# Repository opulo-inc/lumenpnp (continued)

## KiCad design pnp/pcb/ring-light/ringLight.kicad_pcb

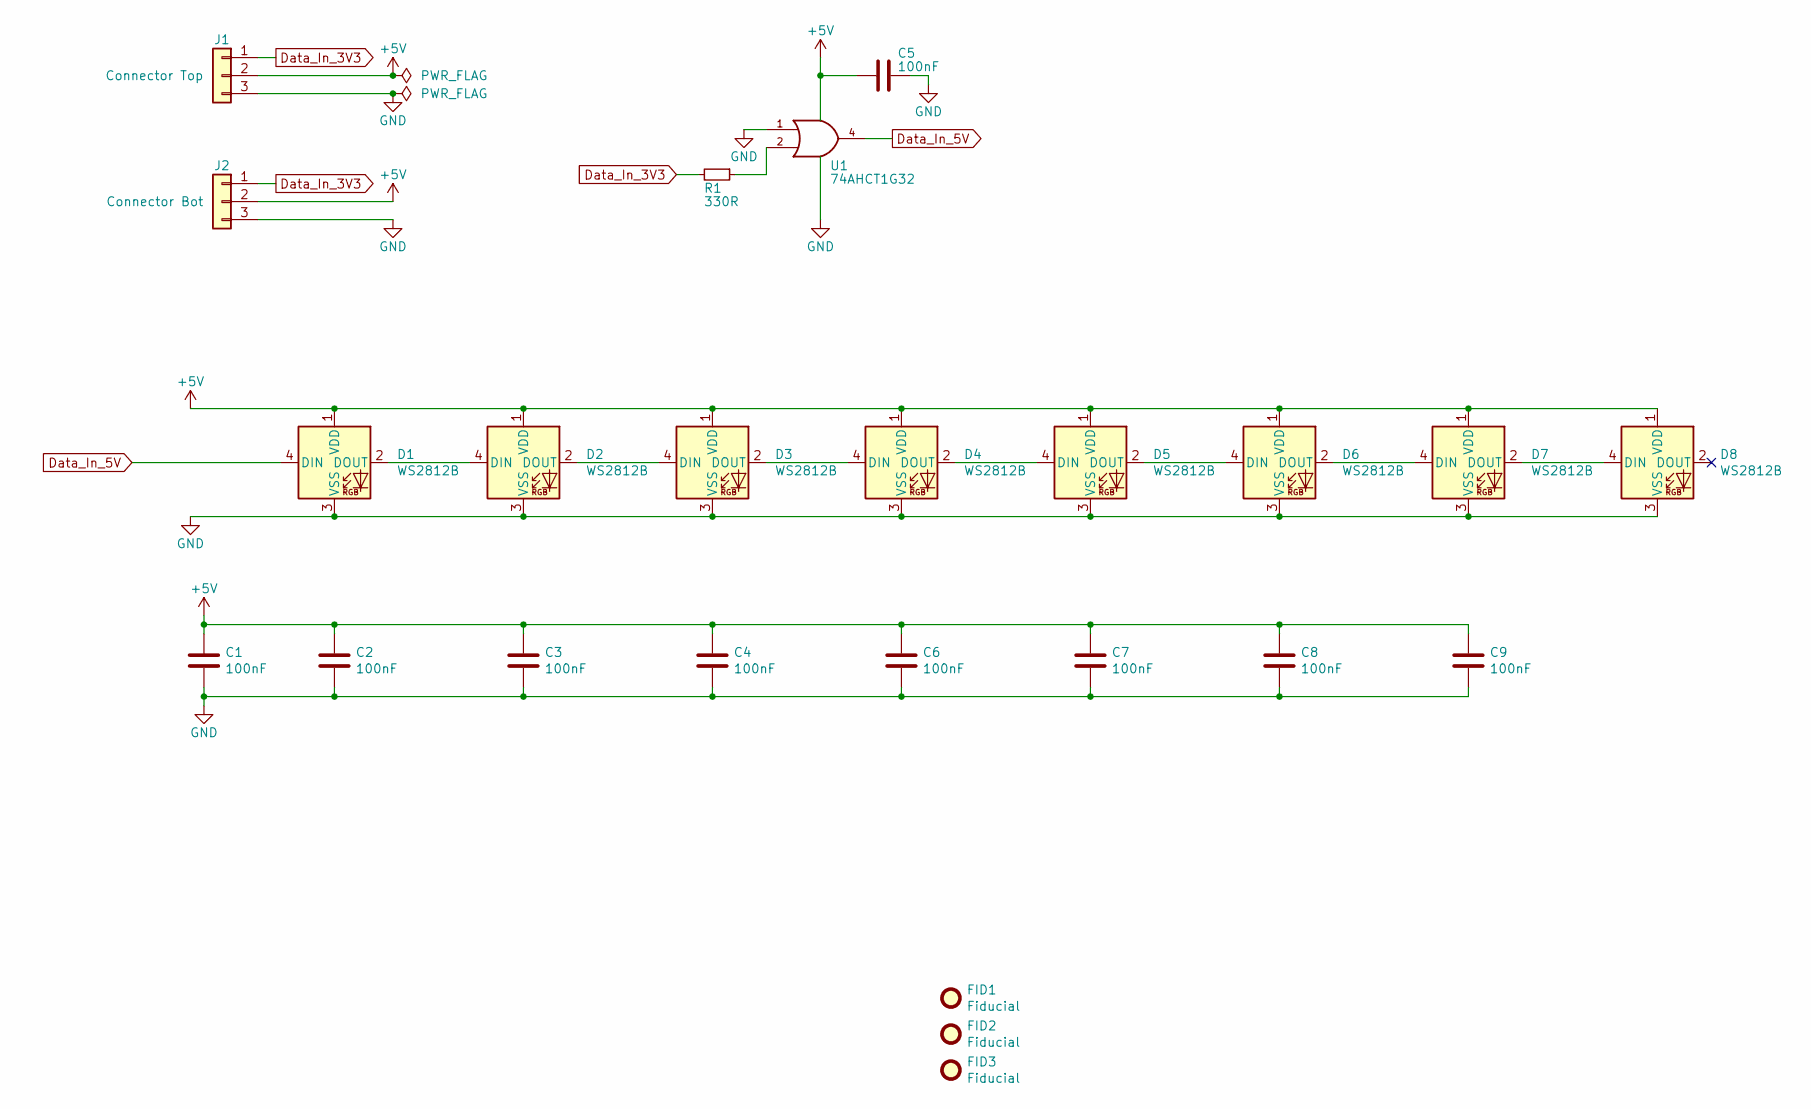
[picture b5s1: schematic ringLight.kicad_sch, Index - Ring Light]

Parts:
C1, C2, C3, C4, C5, C6, C7, C8, C9: 100nF; C_0805_2012Metric; Part # CC0805KRX7R9BB104; JLCPCB C49678
D1, D2, D3, D4, D5, D6, D7, D8: WS2812B; LED_WS2812B_PLCC4_5.0x5.0mm_P3.2mm; Part # WS2812B; JLCPCB C114586
FID1, FID2, FID3: Fiducial; Fiducial_1mm_Mask2mm
J1: Connector Top; JST_XH_B3B-XH-A_1x03_P2.50mm_Vertical; Part # B3B-XH-A(LF)(SN); JLCPCB C144394
J2: Connector Bot; JST_XH_S3B-XH-A-1_1x03_P2.50mm_Horizontal; Part # S3B-XH-A-1(LF)(SN); JLCPCB C163036
R1: 330R; R_0805_2012Metric; Part # 0805W8F3300T5E; JLCPCB C17630
U1: 74AHCT1G32; SOT-353_SC-70-5; Part # SN74AHCT1G32DCKR; JLCPCB C350558

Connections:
+5V: C1.1, C2.1, C3.1, C4.1, C5.1, C6.1, C7.1, C8.1, C9.1, D1.1 (VDD), D2.1 (VDD), D3.1 (VDD), D4.1 (VDD), D5.1 (VDD), D6.1 (VDD), D7.1 (VDD), D8.1 (VDD), J1.2, J2.2, U1.5 (VCC)
Data_In_3V3: J1.1, J2.1, R1.2
Data_In_5V: D1.4 (DIN), U1.4
GND: C1.2, C2.2, C3.2, C4.2, C5.2, C6.2, C7.2, C8.2, C9.2, D1.3 (VSS), D2.3 (VSS), D3.3 (VSS), D4.3 (VSS), D5.3 (VSS), D6.3 (VSS), D7.3 (VSS), D8.3 (VSS), J1.3, J2.3, U1.1, U1.3 (GND)
unnamed: D1.2 (DOUT), D2.4 (DIN)
unnamed: D2.2 (DOUT), D3.4 (DIN)
unnamed: D3.2 (DOUT), D4.4 (DIN)
unnamed: D4.2 (DOUT), D5.4 (DIN)
unnamed: D5.2 (DOUT), D6.4 (DIN)
unnamed: D6.2 (DOUT), D7.4 (DIN)
unnamed: D7.2 (DOUT), D8.4 (DIN)
unnamed: R1.1, U1.2

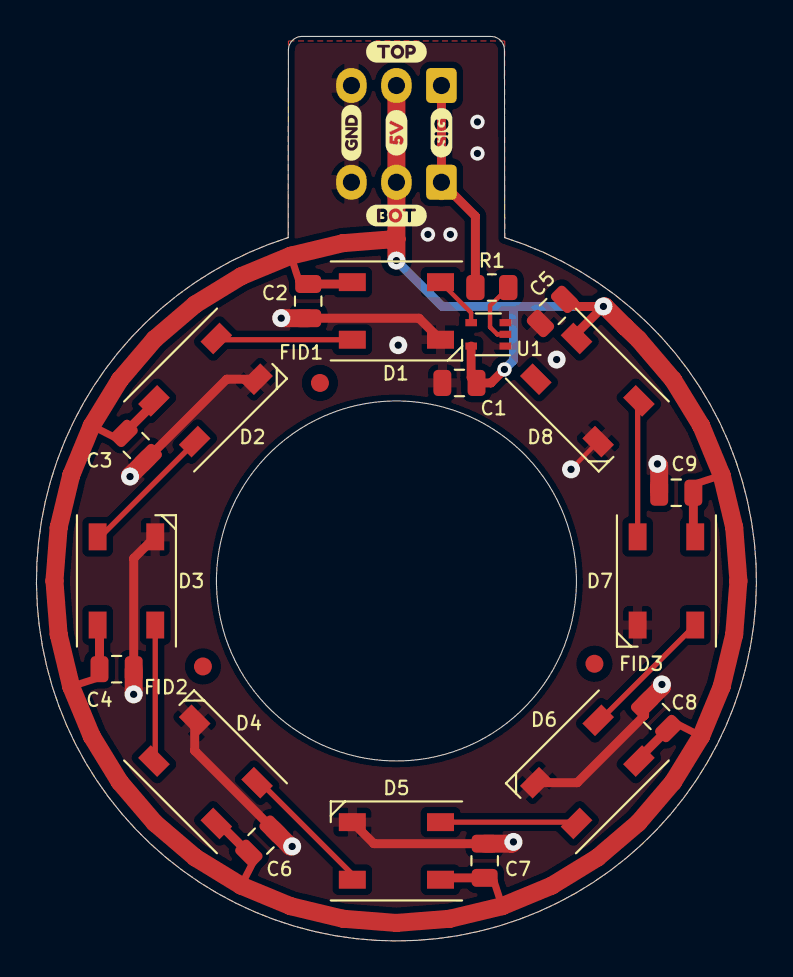
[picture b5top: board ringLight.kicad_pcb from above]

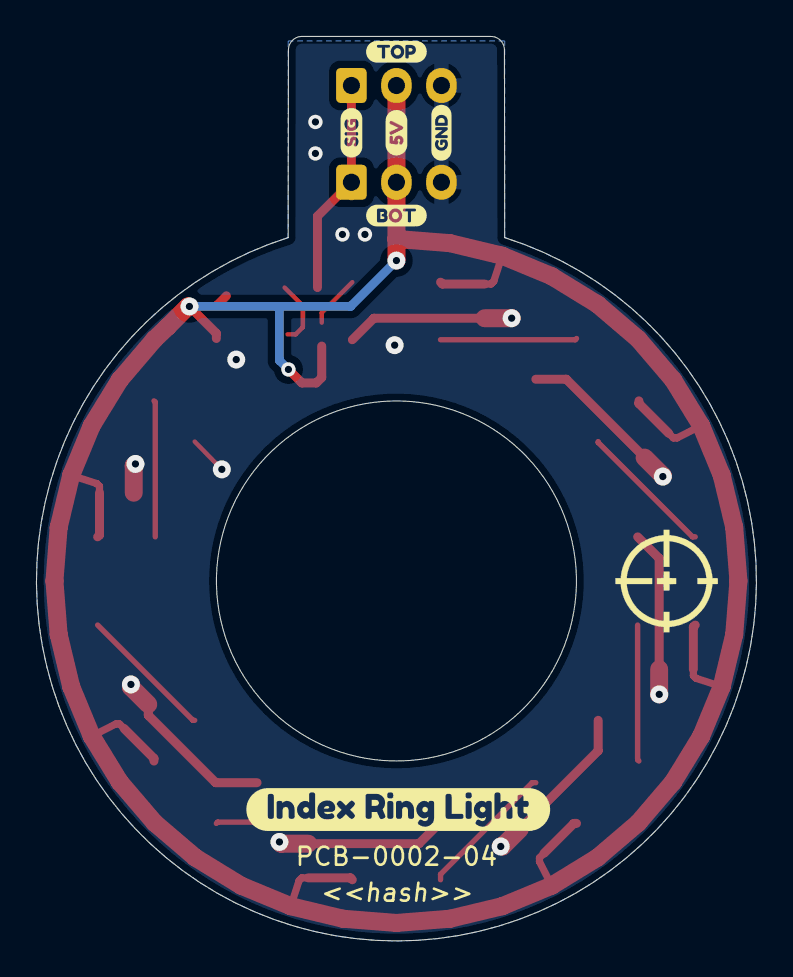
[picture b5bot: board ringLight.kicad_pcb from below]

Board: 2 copper layers, 40.0 x 50.2 mm, 36 parts (8 on the bottom side), 12 nets.

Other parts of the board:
LOGO: LOGO; logo
kibuzzard-61F2BC8D, kibuzzard-61F2BC8D#2: G***; kibuzzard-61F2BC8D
kibuzzard-61F2BC9E, kibuzzard-61F2BC9E#2: G***; kibuzzard-61F2BC9E
kibuzzard-61F2BC96, kibuzzard-61F2BC96#2: G***; kibuzzard-61F2BC96
kibuzzard-61F2BEFE: G***; kibuzzard-61F2BEFE
kibuzzard-61F2BF3C: G***; kibuzzard-61F2BF3C
kibuzzard-61F2BF4A: G***; kibuzzard-61F2BF4A
kibuzzard-61F2BF10: G***; kibuzzard-61F2BF10
svg2mod: n/a; label

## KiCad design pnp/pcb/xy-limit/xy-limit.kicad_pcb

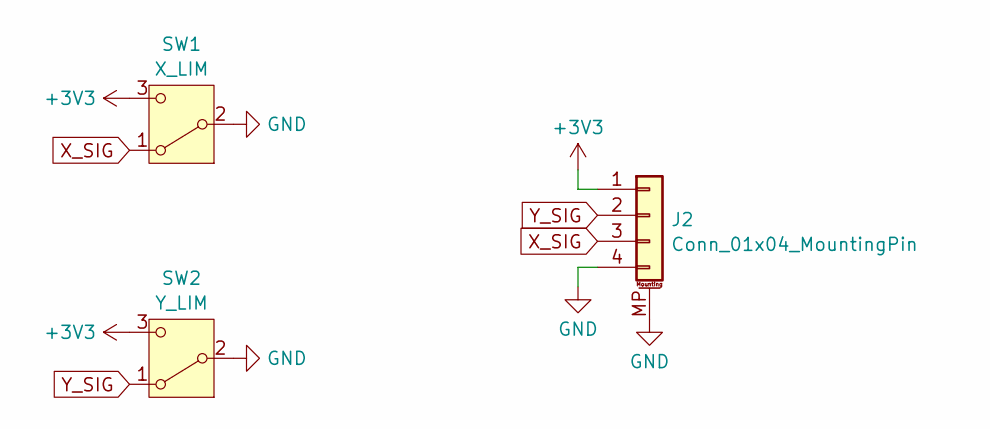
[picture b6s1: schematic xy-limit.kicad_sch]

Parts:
J2: Conn_01x04_MountingPin; JST_PH_B4B-PH-SM4-TB_1x04-1MP_P2.00mm_Vertical
SW1: X_LIM; D2FS-FL-N-A
SW2: Y_LIM; D2FS-FL-N

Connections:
+3V3: J2.1, SW1.3 (C), SW2.3 (C)
GND: J2.4, J2.MP (MountPin), SW1.2 (B), SW2.2 (B)
X_SIG: J2.3, SW1.1 (A)
Y_SIG: J2.2, SW2.1 (A)

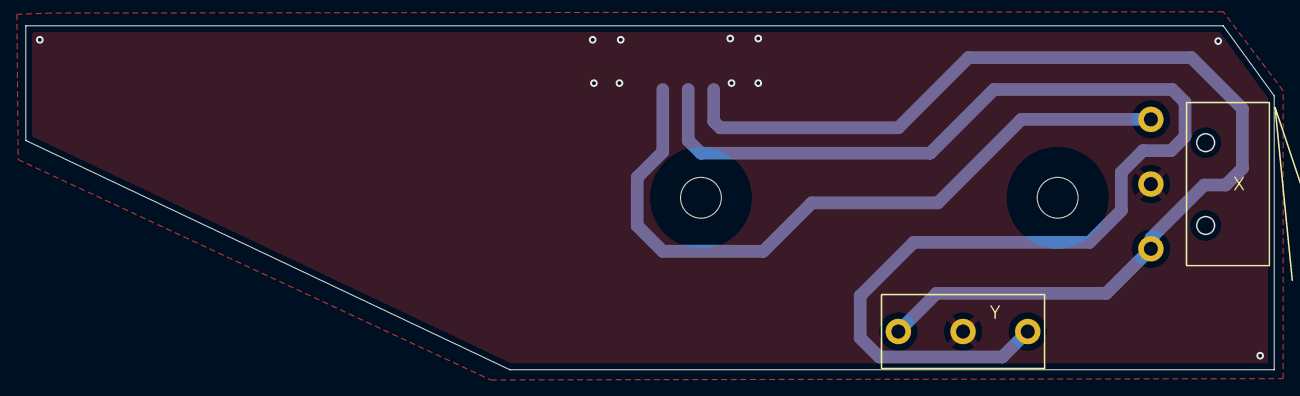
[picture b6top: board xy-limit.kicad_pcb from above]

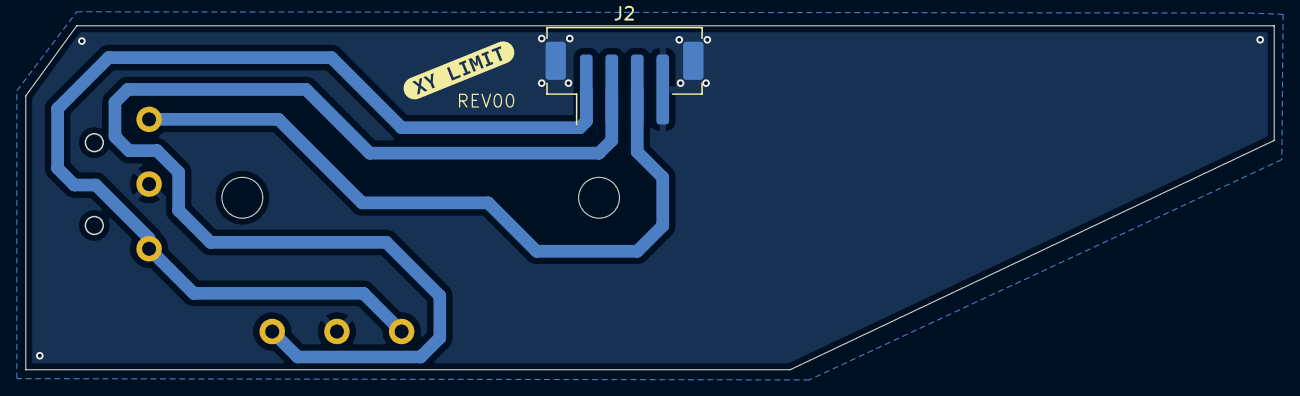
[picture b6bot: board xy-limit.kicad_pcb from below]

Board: 2 copper layers, 98.0 x 27.0 mm, 4 parts (2 on the bottom side), 4 nets.

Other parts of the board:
kibuzzard-65F47CEB: G***; kibuzzard-65F47CEB

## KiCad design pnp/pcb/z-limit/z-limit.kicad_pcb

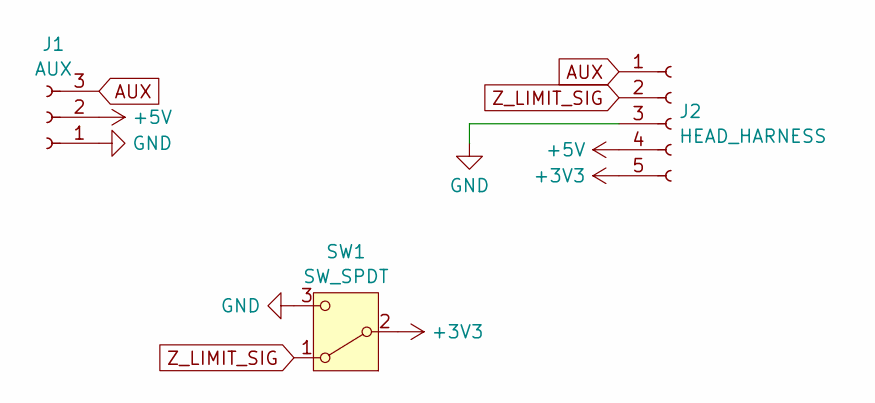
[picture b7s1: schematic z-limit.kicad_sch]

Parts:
J1: AUX; JST_PH_S3B-PH-K_1x03_P2.00mm_Horizontal
J2: HEAD_HARNESS; JST_PH_B5B-PH-SM4-TB_1x05-1MP_P2.00mm_Vertical
SW1: SW_SPDT; D2FS-FL-N-A

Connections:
+3V3: J2.5, SW1.2 (B)
+5V: J1.2, J2.4
AUX: J1.3, J2.1
GND: J1.1, J2.3, J2.MP, SW1.3 (C)
Z_LIMIT_SIG: J2.2, SW1.1 (A)

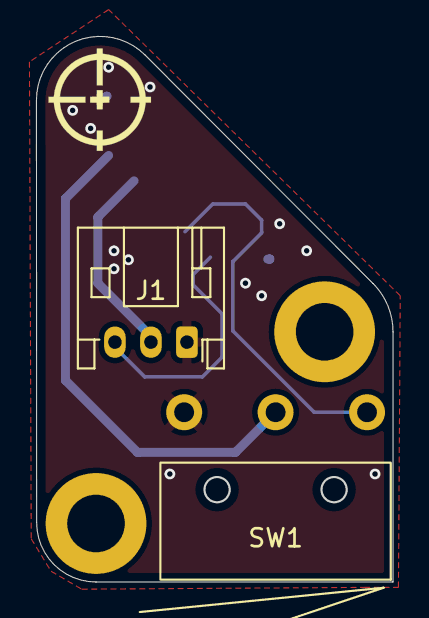
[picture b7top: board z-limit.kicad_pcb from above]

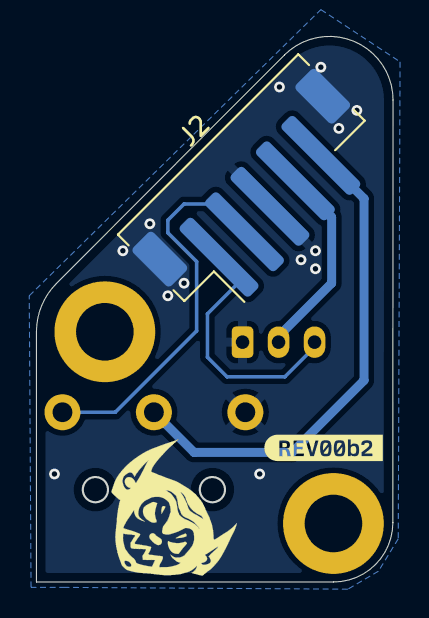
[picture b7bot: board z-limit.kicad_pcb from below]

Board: 2 copper layers, 19.8 x 30.3 mm, 4 parts (2 on the bottom side), 5 nets.

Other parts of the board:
kibuzzard-66478BBC: G***; kibuzzard-66478BBC

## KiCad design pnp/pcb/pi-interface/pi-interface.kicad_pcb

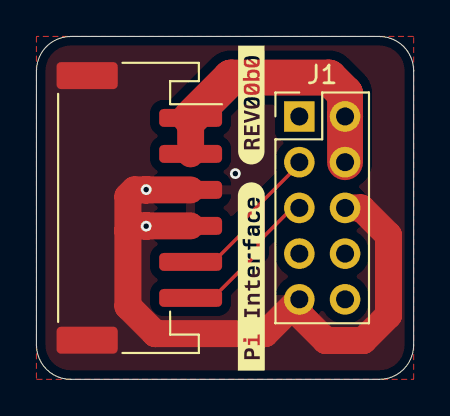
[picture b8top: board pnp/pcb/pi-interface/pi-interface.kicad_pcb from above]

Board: 2 copper layers, 21.0 x 19.1 mm, 4 parts (0 on the bottom side), 4 nets.

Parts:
J1: PI; PinHeader_2x05_P2.54mm_Vertical
Je: MOBO; JST_PH_S6B-PH-SM4-TB_1x06-1MP_P2.00mm_Horizontal
kibuzzard-6647A66F: G***; kibuzzard-6647A66F
kibuzzard-6647A648: G***; kibuzzard-6647A648

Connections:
+5V: J1.2, J1.4, Je.1, Je.2
BOOT: J1.3, Je.5
GND: J1.6, J1.9, Je.3, Je.4, Je.MP (MountPin)
RESET: J1.5, Je.6

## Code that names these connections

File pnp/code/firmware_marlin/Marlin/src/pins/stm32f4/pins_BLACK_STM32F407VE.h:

/**
 * Marlin 3D Printer Firmware
 * Copyright (c) 2020 MarlinFirmware [https://github.com/MarlinFirmware/Marlin]
 *
 * Based on Sprinter and grbl.
 * Copyright (c) 2011 Camiel Gubbels / Erik van der Zalm
 *
 * This program is free software: you can redistribute it and/or modify
 * it under the terms of the GNU General Public License as published by
 * the Free Software Foundation, either version 3 of the License, or
 * (at your option) any later version.
 *
 * This program is distributed in the hope that it will be useful,
 * but WITHOUT ANY WARRANTY; without even the implied warranty of
 * MERCHANTABILITY or FITNESS FOR A PARTICULAR PURPOSE.  See the
 * GNU General Public License for more details.
 *
 * You should have received a copy of the GNU General Public License
 * along with this program.  If not, see <https://www.gnu.org/licenses/>.
 *
 */
#pragma once

/**
 * STM32F407VET6 with RAMPS-like shield
 * 'Black' STM32F407VET6 board - https://www.stm32duino.com/viewtopic.php?t=485
 * Shield - https://github.com/jmz52/Hardware
 */

#if !defined(STM32F4) && !defined(STM32F4xx)
  #error "Oops! Select an STM32F4 board in 'Tools > Board.'"
#elif HOTENDS > 2 || E_STEPPERS > 2
  #error "Black STM32F4VET6 supports up to 2 hotends / E-steppers."
#endif

#ifndef BOARD_INFO_NAME
  #define BOARD_INFO_NAME "Black STM32F4VET6"
#endif

#define DEFAULT_MACHINE_NAME "Index PnP"

//#define I2C_EEPROM
#define SRAM_EEPROM_EMULATION
#define MARLIN_EEPROM_SIZE                0x2000  // 8KB

//
// Servos
//
#define SERVO0_PIN                          PC6
#define SERVO1_PIN                          PC7

//
// Limit Switches
//
#define X_MIN_PIN                           PC13
#define X_MAX_PIN                           PA15
#define Y_MIN_PIN                           PA5
#define Y_MAX_PIN                           PD12
#define Z_MIN_PIN                           PD14
#define Z_MAX_PIN                           PD15

//
// Steppers
//
#define X_STEP_PIN                          PD7
#define X_DIR_PIN                           PD6
#define X_ENABLE_PIN                        PB3

#define Y_STEP_PIN                          PD1
#define Y_DIR_PIN                           PD0
#define Y_ENABLE_PIN                        PD2

#define Z_STEP_PIN                          PE6
#define Z_DIR_PIN                           PE5
#define Z_ENABLE_PIN                        PC13

//E0 is a surrogate for the Rotation stepper, or "R"
#define E0_STEP_PIN                         PE3
#define E0_DIR_PIN                          PE2
#define E0_ENABLE_PIN                       PE4

//E1 is a surrogate for the paste extrusion stepper, or "P"
#define E1_STEP_PIN                         PB5
#define E1_DIR_PIN                          PB4
#define E1_ENABLE_PIN                       PB6

//
// Temperature Sensors
//
#define TEMP_0_PIN                          PC0   // T0
#define TEMP_1_PIN                          PC1   // T1
#define TEMP_BED_PIN                        PC2   // TB

#ifndef TEMP_CHAMBER_PIN
  #define TEMP_CHAMBER_PIN                  PC3   // TC
#endif

//
// Heaters / Fans
//
#define HEATER_0_PIN                        PA2   // Heater0
#define HEATER_1_PIN                        PA3   // Heater1
#define HEATER_BED_PIN                      PA1   // Hotbed

#define FAN_PIN                             PE9   // Fan0
#define FAN1_PIN                            PE11  // Fan1
#define FAN2_PIN                            PE13  // Fan2
#define FAN3_PIN                            PE14  // Fan3

//
// Misc. Functions
//
#define LED_PIN                             PE14
//#define LED_PIN                           PA7
#define KILL_PIN                            PB1

//
// LCD / Controller
//
//#define SD_DETECT_PIN                     PC5
//#define SD_DETECT_PIN                     PA8   // SDIO SD_DETECT_PIN, external SDIO card reader only

#define BEEPER_PIN                          PD10
#define LCD_PINS_RS                         PE15
#define LCD_PINS_ENABLE                     PD8
#define LCD_PINS_D4                         PE10
#define LCD_PINS_D5                         PE12
#define LCD_PINS_D6                         PD1
#define LCD_PINS_D7                         PE8
#define BTN_ENC                             PD9
#define BTN_EN1                             PD4
#define BTN_EN2                             PD13

#define DOGLCD_CS                    LCD_PINS_D5
#define DOGLCD_A0                    LCD_PINS_D6

//
// Onboard SD support
//
#define SDIO_D0_PIN                         PC8
#define SDIO_D1_PIN                         PC9
#define SDIO_D2_PIN                         PC10
#define SDIO_D3_PIN                         PC11
#define SDIO_CK_PIN                         PC12
#define SDIO_CMD_PIN                        PD2

#ifndef SDCARD_CONNECTION
  #define SDCARD_CONNECTION              ONBOARD
#endif

#if SD_CONNECTION_IS(ONBOARD)
  #define SDIO_SUPPORT                            // Use SDIO for onboard SD

  #ifndef SDIO_SUPPORT
    #define SOFTWARE_SPI                          // Use soft SPI for onboard SD
    #define SDSS                     SDIO_D3_PIN
    #define SCK_PIN                  SDIO_CK_PIN
    #define MISO_PIN                 SDIO_D0_PIN
    #define MOSI_PIN                SDIO_CMD_PIN
  #endif
#endif

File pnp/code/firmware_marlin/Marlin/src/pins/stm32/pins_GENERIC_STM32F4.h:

/**
 * Marlin 3D Printer Firmware
 * Copyright (c) 2019 MarlinFirmware [https://github.com/MarlinFirmware/Marlin]
 *
 * Based on Sprinter and grbl.
 * Copyright (c) 2011 Camiel Gubbels / Erik van der Zalm
 *
 * This program is free software: you can redistribute it and/or modify
 * it under the terms of the GNU General Public License as published by
 * the Free Software Foundation, either version 3 of the License, or
 * (at your option) any later version.
 *
 * This program is distributed in the hope that it will be useful,
 * but WITHOUT ANY WARRANTY; without even the implied warranty of
 * MERCHANTABILITY or FITNESS FOR A PARTICULAR PURPOSE.  See the
 * GNU General Public License for more details.
 *
 * You should have received a copy of the GNU General Public License
 * along with this program.  If not, see <http://www.gnu.org/licenses/>.
 *
 */
#pragma once

/**
 * To build with Arduino IDE use "Discovery F407VG"
 * To build with PlatformIO use environment "STM32F4"
 */
#if !defined(STM32F4) && !defined(STM32F4xx)
  #error "Oops! Select an STM32F4 board in 'Tools > Board.'"
#elif HOTENDS > 2 || E_STEPPERS > 2
  #error "STM32F4 supports up to 2 hotends / E-steppers."
#endif

#define BOARD_INFO_NAME      "Index Mobo"
#define DEFAULT_MACHINE_NAME "Index PnP"

//#define I2C_EEPROM

#ifndef E2END
  #define E2END 0xFFF // 4KB
#endif

// Ignore temp readings during development.
//#define BOGUS_TEMPERATURE_GRACE_PERIOD 2000

//
// Limit Switches
//
#define X_MIN_PIN          PE0
#define X_MAX_PIN          -1
#define Y_MIN_PIN          PE1
#define Y_MAX_PIN          -1
#define Z_MIN_PIN          PE14
#define Z_MAX_PIN          -1

//
// Z Probe (when not Z_MIN_PIN)
//

//#ifndef Z_MIN_PROBE_PIN
//  #define Z_MIN_PROBE_PIN  PA4
//#endif

//
// Steppers
//

#define X_STEP_PIN         PD7
#define X_DIR_PIN          PD6
#define X_ENABLE_PIN       PB3
//#ifndef X_CS_PIN
//  #define X_CS_PIN         PD1
//#endif

#define Y_STEP_PIN         PE11
#define Y_DIR_PIN          PE10
#define Y_ENABLE_PIN       PE13
//#ifndef Y_CS_PIN
//  #define Y_CS_PIN         PE12
//#endif

#define Z_STEP_PIN         PD6
#define Z_DIR_PIN          PD7
#define Z_ENABLE_PIN       PD4
//#ifndef Z_CS_PIN
//  #define Z_CS_PIN         PD5
//#endif

#define E0_STEP_PIN        PB5
#define E0_DIR_PIN         PB6
#define E0_ENABLE_PIN      PB3
//#ifndef E0_CS_PIN
//  #define E0_CS_PIN         PB4
//#endif

#define E1_STEP_PIN        PE4
#define E1_DIR_PIN         PE2
#define E1_ENABLE_PIN      PE3
//#ifndef E1_CS_PIN
//  #define E1_CS_PIN         PE5
//#endif

#define SCK_PIN            PA5
#define MISO_PIN           PA6
#define MOSI_PIN           PA7

//
// Temperature Sensors
//

#define TEMP_0_PIN         PC0   // Analog Input
#define TEMP_1_PIN         PC1   // Analog Input
#define TEMP_BED_PIN       PC2   // Analog Input

//
// Heaters / Fans
//

#define HEATER_0_PIN       PA1
#define HEATER_1_PIN       PA2
#define HEATER_BED_PIN     PA0

#ifndef FAN_PIN
  #define FAN_PIN          PC6
#endif
#define FAN1_PIN           PC7
#define FAN2_PIN           PC8

#define ORIG_E0_AUTO_FAN_PIN  FAN1_PIN // Use this by NOT overriding E0_AUTO_FAN_PIN

//
// Misc. Functions
//

//#define CASE_LIGHT_PIN_CI PF13
//#define CASE_LIGHT_PIN_DO PF14
//#define NEOPIXEL_PIN      PF13

//
// Průša i3 MK2 Multi Material Multiplexer Support
//

//#define E_MUX0_PIN         PG3
//#define E_MUX1_PIN         PG4

//
// Servos
//

//#define SERVO0_PIN         PE13
//#define SERVO1_PIN         PE14


#define SDSS               PE7
#define SS_PIN             PE7
#define LED_PIN            PB7         //Alive
#define PS_ON_PIN          PA10
#define KILL_PIN           PA8
#define PWR_LOSS           PA4         //Power loss / nAC_FAULT

//
// LCD / Controller
//

#define SD_DETECT_PIN      PA15
#define BEEPER_PIN         PC9
#define LCD_PINS_RS        PE9
#define LCD_PINS_ENABLE    PE8
#define LCD_PINS_D4        PB12
#define LCD_PINS_D5        PB13
#define LCD_PINS_D6        PB14
#define LCD_PINS_D7        PB15
#define BTN_EN1            PC4
#define BTN_EN2            PC5
#define BTN_ENC            PC3

//
// Filament runout
//

#define FIL_RUNOUT_PIN     PA3

//
// ST7920 Delays
//
#if HAS_GRAPHICAL_LCD
  #define BOARD_ST7920_DELAY_1 DELAY_NS(96)
  #define BOARD_ST7920_DELAY_2 DELAY_NS(48)
  #define BOARD_ST7920_DELAY_3 DELAY_NS(715)
#endif

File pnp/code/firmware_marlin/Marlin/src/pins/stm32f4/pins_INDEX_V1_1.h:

/**
 * Marlin 3D Printer Firmware
 * Copyright (c) 2020 MarlinFirmware [https://github.com/MarlinFirmware/Marlin]
 *
 * Based on Sprinter and grbl.
 * Copyright (c) 2011 Camiel Gubbels / Erik van der Zalm
 *
 * This program is free software: you can redistribute it and/or modify
 * it under the terms of the GNU General Public License as published by
 * the Free Software Foundation, either version 3 of the License, or
 * (at your option) any later version.
 *
 * This program is distributed in the hope that it will be useful,
 * but WITHOUT ANY WARRANTY; without even the implied warranty of
 * MERCHANTABILITY or FITNESS FOR A PARTICULAR PURPOSE.  See the
 * GNU General Public License for more details.
 *
 * You should have received a copy of the GNU General Public License
 * along with this program.  If not, see <https://www.gnu.org/licenses/>.
 *
 */
#pragma once

/**
 * Custom STM32F407VET6/VGT6 pick and place machine board
 * based on the BLACK_STM32F407VE6 pin mapping.
 * 
 * https://www.github.com/sphawes/index
 * Motherboard REV02
 */

#if !defined(STM32F4) && !defined(STM32F4xx)
  #error "Oops! Select an STM32F4 board in 'Tools > Board.'"
#elif HOTENDS > 3 || E_STEPPERS > 3
  #error "Index V1.1 supports up to 3 E-steppers."
#endif

#ifndef BOARD_INFO_NAME
  #define BOARD_INFO_NAME "Index Motherboard"
#endif

#define DEFAULT_MACHINE_NAME "Index Pick and Place"

//#define I2C_EEPROM
#define SRAM_EEPROM_EMULATION
#define MARLIN_EEPROM_SIZE                0x2000  // 8KB

// No power supply control, or kill switch
#define PS_ON_PIN                           -1
#define KILL_PIN                            -1

//
// Servos
//
#define SERVO0_PIN                          PE13
#define SERVO1_PIN                          PE14

//
// Limit Switches
//
#define X_MIN_PIN                           PE8
#define X_MAX_PIN                           -1
#define Y_MIN_PIN                           PE9
#define Y_MAX_PIN                           -1
#define Z_MIN_PIN                           PE10
#define Z_MAX_PIN                           -1

//
// Steppers
//
#define X_STEP_PIN                          PB3
#define X_DIR_PIN                           PD7
#define X_ENABLE_PIN                        PB5
#ifndef X_CS_PIN
  #define X_CS_PIN                          PB4
#endif

#define Y_STEP_PIN                          PD0
#define Y_DIR_PIN                           PC12
#define Y_ENABLE_PIN                        PD2
#ifndef Y_CS_PIN
  #define Y_CS_PIN                          PD1
#endif

#define Z_STEP_PIN                          PE5
#define Z_DIR_PIN                           PE4
#define Z_ENABLE_PIN                        PC13
#ifndef Z_CS_PIN
  #define Z_CS_PIN                          PE6
#endif

//E0 is a surrogate for the Rotation stepper, or "R"
//T0
#define E0_STEP_PIN                         PE1
#define E0_DIR_PIN                          PE0
#define E0_ENABLE_PIN                       PE3
#ifndef E0_CS_PIN
  #define E0_CS_PIN                         PE2
#endif

//E1 is a surrogate for the paste extrusion stepper, or "P"
//T1
#define E1_STEP_PIN                         PB7
#define E1_DIR_PIN                          PB6
#define E1_ENABLE_PIN                       PB9
#ifndef E1_CS_PIN
  #define E1_CS_PIN                         PB8
#endif

//E2 is a surrogate for the "C" stepper
//T2
#define E2_STEP_PIN                         PD4
#define E2_DIR_PIN                          PD3
#define E2_ENABLE_PIN                       PD6
#ifndef E2_CS_PIN
  #define E2_CS_PIN                         PD5
#endif

//
// Temperature Sensors ( i.e. "ANALOG" input )
//
#define TEMP_0_PIN                          PC2   // T0
#define TEMP_1_PIN                          PC3   // T1
#define TEMP_2_PIN                          PC3   // T2

#if HAS_TMC_UART
  /**
   * TMC2208/TMC2209 stepper drivers
   * Software serial
   */

  #define X_SERIAL_TX_PIN                  PB4
  #define X_SERIAL_RX_PIN                  PB4

  #define Y_SERIAL_TX_PIN                  PD1
  #define Y_SERIAL_RX_PIN                  PD1

  #define Z_SERIAL_TX_PIN                  PE6
  #define Z_SERIAL_RX_PIN                  PE6

  #define E0_SERIAL_TX_PIN                 PE2
  #define E0_SERIAL_RX_PIN                 PE2

  #define E1_SERIAL_TX_PIN                 PB8
  #define E1_SERIAL_RX_PIN                 PB8

  #define E2_SERIAL_TX_PIN                 PD5
  #define E2_SERIAL_RX_PIN                 PD5

  // Reduce baud rate to improve software serial reliability
  #define TMC_BAUD_RATE                    19200
#endif

//
// Heaters
// 
#define HEATER_0_PIN                        PA1
#define HEATER_1_PIN                        PA1
#define HEATER_2_PIN                        PA1

// "FAN" pin ( MOSFETS )
#ifndef FAN_PIN
  #define FAN_PIN                           PC6 // Mosfet 1
#endif
#define FAN1_PIN                            PD15 // Mosfet 2
#define FAN2_PIN                            PD14 // Mosfet 3
#define FAN3_PIN                            PD13 // Mosfet 4
#define FAN4_PIN                            PC1 // VAC_1_SIG
#define FAN_SOFT_PWM                        // slow software PWM rather than hardware

// Neopixel Rings
#define NEOPIXEL_PIN                        PE11 
#define NEOPIXEL2_PIN                       PE12

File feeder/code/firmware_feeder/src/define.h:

#define DE   PA12
#define _RE  PA11

#define LED1 PB0   //yellow, on bottom of front face
#define LED2 PA7   //green, on top of front face
#define LED3 PB11  //green, first on top face
#define LED4 PB10  //green, second on top face
#define LED5 PB1   //green, third on top face

#define SW1 PA5
#define SW2 PA6

#define DRIVE1   PB6
#define DRIVE2   PB7
#define PEEL1    PB9
#define PEEL2    PB8

#define ONE_WIRE PA2
#define FILM_TENSION  PA3

#define VCNT2020 PA1
#define QRE1113  PA4
//-----------------------
#define OPTO_SIG QRE1113



#define LONG_PRESS_DELAY 300

//#define DEBUG
//#define OPTO_DEBUG

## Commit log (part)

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2023-05-10 Removed unused files from FDM folder
2023-05-12 adds note in bom about printing bottom and top light mount in white filament
2023-05-12 updates ci ecad export container to support kicad7
2023-05-12 removes failing build with ERC errors
2023-05-12 replaces polygon edge cuts outline of ftp with lines to work around pcbdraw rendering bug
2023-05-15 updates openpnp config files in the repo
2023-05-15 fixes #622
2023-05-31 x-toolhead-asm electronics improvements
    - Adds WIP top-camera-cover to protect exposed top-camera PCB
    - This cover still requires raised protrusions to space it away and prevent collisions with the SMT components on the PCB
    - Adds new region to top-light-cover to cover exposed top-ring-light THT pins
    - Rotates toolhead motors 90º to reduce cable strain
    - Adds notch in z-gantry to create clearance for nema-11 toolhead motor
    - Adds zip tie channel in z-gantry to create cable strain relief point for L/R toolhead cable
2023-06-02 Finalizes top-camera assembly improvements
    - Also introduces concept of lumenpnp lower stand
2023-06-12 Adds top and bottom vision planes to CAD assembly
2023-06-12 Adds n08-nozzle to each toolhead
2023-06-12 fixes path error in openpnp config ci export script
2023-06-20 changes footprints for tht connectors, removes stepper driver module in exchange for a dedicated TMC2226 driver implemented on the board
2023-06-29 Misc changes
    - Adds 32mm strip feeder to repo
    - Updates 24mm strip feeder design
    - Updates hole dia on mobo-bottom-cover
2023-07-11 imports new TVS and inline resistors into pcb
2023-07-14 Remove ferrite on GND
2023-07-29 Remove lock file from git
2023-07-30 Motor driver new Symbol and fix TVS placement
2023-07-30 Add link to check symbol approval status
2023-08-01 Removes 3D models of unused parts from CAD repo
    - Removes vslot-roller as it has been fully eliminated in the switch to linear rail
    - Removes allen-wrench-holder due to Opulo switching this to a purchased item
    - Removes MS4M-M5 in preparation for switch to rotary-pnumatic-adapter
2023-08-01 Updates datum-board-mount for symmetry (DFA Improvement)
    - Adds large chamfers to bottom side to support installation in both +180º/-180º orientation without issue
2023-08-01 Updates v3.1.0 assembly for recent changes
    - Removes 3D models of unused parts from ASM
    - Adds rotary-pneumatic-adapter.FCStd to ASM
    - Adds updated version of datum-board-mount
2023-08-02 Begins removing x-gantry-block upper and lower from v3.1.0 design
2023-08-09 adds head cable harness which integrates all other head cables
2023-08-14 adds other files for cad freeze
2023-08-22 Addresses observations from v3.1.0 PVT build
    CAD changes made:
    ⁃ Rounded the ends of the tensioner mounting arms in x-idler-mount to match style of front-####-leg
    ⁃ Added a mid-air hole overhang feature to front-drag-chain-mount’s hex-nut pockets
    ⁃ Tightened the hex-nut pocket on front-left-leg to keep drag-chain mount’s attachment nut in place during transit
    ⁃ Labeled back-leg’s y-stepper wire outlet ports with which side each port is for to help avoid assembly mistakes
    ⁃ Labeled y-gantry-left’s back-leg wire outlet “Y1”
2023-08-25 All pages checked
2023-08-27 Mobo parts sourced
2023-08-28 Pre-release cleanup work
    - Increased through-hole dia on mobo-bottom-cover to 4mm
    - Slots nozzle-rack to allow for easy removal with 2x M3x10-hex-head and 2x M3-wing-nut
    - Begins work on new strip feeder design for 8mm through 32mm
    - Begins to prep bom.csv for next release
2023-08-29 continues bom finalization work
2023-09-01 Removed alt-view cad assemblies
    removed from repo after no longer needing them during OHAI authoring
2023-09-04 Fix small typo
2023-09-06 Reverts strip-feeder designs back to v3.0.5 style
2023-09-08 updates mcad export to use freecad 0.21.1
2023-09-13 Create x-cable-chain-bracket-alt.FCStd
    Creates x-cable-chain-bracket-alt for use with LDO-sourced drag chain
2023-09-14 Updated workflow to FreeCAD 0.21.1
2023-09-14 Do the same for DXFs
2023-09-16 Schematic almost finished
2023-09-16 Updates feeders
2023-09-20 Adds bump to 8mm strip feeder for label poke-yoke
2023-09-29 Updates 24mm for hole tolerance and sticker
2023-10-02 Fixes adj-strip-feeder for STL export
    Converts the two sides of adj-strip-feeder into a compound shape named "body" so that the BOM utility may render both sides and export an STL comprised of two bodies.
2023-10-02 updates BOM for broken images
2023-10-12 Updates front-left-leg for m5-square-nut
    Updates front-left-leg to support an m5-square-nut for use with the front-drag-chain-mount attachment bolt.
2023-10-13 Updates assembly for `M5-square-nut` in `y-gantry-left`
    Loads in latest model of `front-left-leg`
2023-10-24 Hotfix 8mm-strip-feeder tolerances
2023-10-29 Finished reverse polarity and inrush current circuits
2023-11-01 Reverse polarity placement
2023-11-12 Placement study of motor drivers
2023-11-24 Update x-cable-chain-bracket-alt.FCStd
    Removes proxy models of neighboring drag-chain wire covers
2023-12-11 Fix build-marlin.yml to use correct folder names
2023-12-22 beta 0 build
2024-01-11 Updates asm to pull in current v3.1
2024-01-22 continues electronics enclosure development
2024-01-25 Fix FreeCAD AppImage name
2024-01-30 Updates note for m3x12-self-tapping in bom
2024-02-01 adds out folders to gitignore
2024-02-01 adds v3.1+ openpnp configs
2024-02-05 Renames body001 to body in static-camera-foot
2024-02-08 Adds wireviz data for the blade-harness-set
2024-02-23 pulls v3.2.0 changes into branch
2024-02-27 remodels mobo-mount
2024-03-11 begins work on nozzle redesign
2024-03-11 Replaces cp40-holder with nozzle-holder
2024-03-13 continues work
2024-03-21 updates front-drag-chain-mount
2024-03-21 adds and updates to the kicad lib to support new components
2024-03-21 adds pcb 3d models
2024-03-21 adds z limit board and xy board
2024-03-21 adds correct lengths to cable harnesses
2024-03-21 ignoring kicad lock files
2024-03-21 updates 3d models of z and XY limit pcbs in freecad
2024-03-22 adds PH blades. currently a separate file for 12 and 13 variants with silks in the files for each variation
2024-03-25 ring light: update pcb from sch (only text fields changed)
2024-03-25 ring light: change LCSC part number to match footprint (and add part# field)
2024-03-29 adds lots of 3d models
2024-04-01 adds first pass at wireviz ci
2024-04-01 adds cable harness export
2024-04-02 continues work on xy drag chain system
2024-04-02 adds copper keepout to blade countersink holes
2024-04-03 Updates toolhead assembly to remove top-camera-mount
2024-04-16 Update Mobo KiCAD files to v8
2024-04-16 Set logos as not part of Schematic
2024-04-16 Give unique references to Goblin and Opulo logos on PCB
2024-04-17 Update PCBs to KiCAD 8
2024-04-17 Fix fiducial reference designators
2024-04-17 Fix CI
2024-04-17 remove dangling file
2024-04-17 Fix graphics propoerties
2024-04-17 Fix 3D files
2024-04-17 Fix mounting holes
2024-04-17 Sourcing complete
2024-04-18 Fix part sourcing
2024-04-19 Sourcing of ESD dodes
2024-05-14 Continues cad work
2024-05-15 updates git ignore
2024-05-17 updates zlimit to rev00b2 with fixed switch pinout
2024-05-18 tightens back
2024-05-22 updates z limit pcb, adds extra optional boards
2024-05-22 Tightens the hex nut pockets on y-gantry
2024-05-24 Update export-ecad.yaml to support kicad8
2024-05-24 updates name of opulo logo reference to fix kibot export
2024-05-24 gives all footprints a symbol
2024-05-24 Update config-4layer.kibot.yaml to remove ibom
2024-05-30 Adds host power port knockout
2024-06-07 adds new mobo enclosure
2024-06-11 Syncs repo with latest changes
2024-06-12 more cad
2024-06-20 semi-finalizes mobo-mount + updates bottom-camera-cover for arducam
2024-06-20 updates x-gantry-drag-chain mounting holes on cable-splay
2024-06-20 dissolves drag-chain-asm files into main asm
2024-06-20 makes y-front-drag-chain-mount prettier
2024-06-20 tunes valve mounting feature on mobo-mount
2024-06-20 updates asm for daily changes
2024-06-22 improves ring-light diffusion
2024-06-25 shortens y-limit-striker
2024-06-25 Adds notch for camera cables in x-gantry-back
2024-06-25 adjusts cable connector cutout position in bottom-camera-cover
2024-06-25 updates asm for latest changes
2024-06-25 makes enclosure lid easier remove while installed
2024-06-26 cleans up mobo-mount geometry + adds y-drag-chain mounting feature
2024-06-26 Makes y-limit-striker adjustable
2024-07-03 Minimizes cable-splay
2024-07-03 adds adj y-limit-striker to asm
2024-07-18 Removes Opulo Nozzle Project from Repo
2024-07-18 Strengthens y-limit-striker
2024-07-18 Updates bottom-camera-assembly to support screwed-in static-camera-foot
2024-07-18 Updates z-gantry to prevent rubbing on x-idler-pulley bolt
2024-07-18 Removes reference to IDC connectors from CAD
2024-07-19 creates group in asm for bolt kit bag items
2024-07-27 Adds labels to repo
2024-07-27 Recolors nema-11-motor
2024-07-27 Makes static-camera-foot less ugly
2024-07-27 Removes zip-tie lug from x-gantry-front
2024-07-27 removes unmaintained models from repo
2024-07-27 removes flexural pump-mount from repo
2024-08-07 preps repo for release
2024-08-09 Renames linear rail components
2024-08-09 Replaces generic camera CAD with specific top/bottom models
2024-08-09 Fixes hole depth for m3-thumb-screw in bottom-camera-mount
2024-08-09 Moves host controller box to misc folder for later use
2024-08-09 Updates reducing-union-tee-4-6-4 mounting geometry
2024-08-09 Updates asm for latest changes + reformats feature tree
2024-08-12 Removes obsolete pump mount designs from repo
2024-08-12 Removes unused STEP files from repo
2024-08-12 removes reference geometry folder
2024-08-12 Adds usb connector and vacuum sensors to mobo-rev05 CAD
2024-08-12 Widens x-motor-mount / x-idler-mount to 20.5mm extrusion pocket
2024-08-12 Updates BOM and ASM for v4.0.0 release prep
    👀
2024-08-12 Attempts to fix diag tree bug in nozzle-camera-mask
2024-08-12 Removes mobo-mount and mobo-cover CAD from repo
2024-08-12 Attempts to fix broken static-camera-foot image
2024-08-13 Bakes out static-camera-foot design history
2024-08-28 adds hero
2024-09-01 Adjusts tolerances of select FDM parts for easier assembly and less glue
2024-09-01 Adds modeled-in supports to control-box wire inlet port
2024-09-01 Updates bottom-light-mount to support new wide angle lens in bottom-camera
2024-09-01 update license and readme
2024-09-01 removes built-with badges from repo to be moved to another
2024-09-01 adds camera cables and freecad file for x cable chain
2024-09-01 updates cable lengths
2024-09-01 updates bom
2024-09-01 updates workflow
2024-09-01 click version printed
2024-09-03 adds opnp configs
2024-09-09 Makes print-in-place support wider for control-box
2024-09-09 fixes mcad
2024-09-13 reverts ring light to original design with level shifters
2024-10-02 Adds better print-in-place support to control-box
2024-10-15 opens up the mounting slots on the left side of the x cable chain support pcb to account for fit
2024-10-16 small silkscreen tweak on blade12, updates freecad models, adds to assembly
2024-11-22 updates y-gantry-left for test assembly
2024-12-23 prep for 401
2024-12-26 Remove last empty line in bom
2024-12-31 Add comment for nozzle-rack about filament color
2025-01-01 improve cv-pipeline for nozzle tips in machine.xml
2025-01-09 Widens blades to better feeder fit
2025-01-10 adds cable chain support with slightly larger mounting slots
2025-01-10 fixes x bottom camera offset
2025-01-21 exported rev01b0 of staging plate
2025-07-14 adds 0402 ftp
2025-07-14 fixed path error
